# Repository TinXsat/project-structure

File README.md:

# project-structure

This repo is purely for discussing and planning the whole project's structure - what will communicate with what and how, how software will be organised, etc - whole "schema"

### Contributing :pencil:
All discusion and changes will be done through Pull Requests and Issues - commiting directly to master is officially illegal here  :no_entry_sign: :hand: :no_entry:

<sub><sub>[Inserting emojis](https://gist.github.com/rxaviers/7360908) into every single header is also required, and not respecting that will be punished 🔪 </sub></sub>

<!-- START doctoc generated TOC please keep comment here to allow auto update -->
<!-- DON'T EDIT THIS SECTION, INSTEAD RE-RUN doctoc TO UPDATE -->
**Table of Contents**

- [Mission :rainbow:](#mission-rainbow)
  - [Measurements of atmospheric pressure and temperature with subsequent data analysis :thermometer:](#measurements-of-atmospheric-pressure-and-temperature-with-subsequent-data-analysis-thermometer)
    - [Key goals :key:](#key-goals-key)
  - [Demonstration of cansat system for rescue operations during natural disasters :volcano:](#demonstration-of-cansat-system-for-rescue-operations-during-natural-disasters-volcano)
    - [Key goals :key:](#key-goals-key-1)
    - [Optional goals :small_blue_diamond:](#optional-goals-small_blue_diamond)
- [Satellite :satellite:](#satellite-satellite)
  - [Satellite launch :rocket:](#satellite-launch-rocket)
  - [Sensors aboard :thermometer:](#sensors-aboard-thermometer)
  - [Satellite 2 ground communication :phone:](#satellite-2-ground-communication-phone)
- [Ground station :radio:](#ground-station-radio)
- [Ground back-end server :computer:](#ground-back-end-server-computer)
- [Front-end :iphone:](#front-end-iphone)
- [Further data analisys :bar_chart:](#further-data-analisys-bar_chart)
- [Gantt timeline chart :alarm_clock:](#gantt-timeline-chart-alarm_clock)

<!-- END doctoc generated TOC please keep comment here to allow auto update -->

# Mission :rainbow:
## Measurements of atmospheric pressure and temperature with subsequent data analysis :thermometer:

### Key goals :key:

 - Measure of pressure and temperature outside the cansat.
 - Radio transmission of measurements data in minimal rate one packet per second.
 - Calculation of altitude based on atmospheric pressure.

## Demonstration of cansat system for rescue operations during natural disasters :volcano:

### Key goals :key:

 - Design system that meet following requirements:
 - low cost of produce
 - high accuracy
 - Access to information about position(GPS), altitude (barometer), temperature, acceleration
 - Take photos from the thermovision and visible range camera.
 - Mark on photos all obstacles (to protect rescuers) and places where people could possibly be.

### Optional goals :small_blue_diamond:

 - Investigate fire resistant biofiber composite with which body of cansat will be build
 - Pointing geographical coordinates of marked obstacles/humans.

# Satellite :satellite:
How the cansat sattelite will look and work to help us do the mission?

## Satellite launch :rocket:
How we will actually launching the sattelite (that is take it to 1.5km above)?

## Sensors aboard :thermometer:

## Satellite 2 ground communication :phone:
How our satellite will communicate with the ground station?

# Ground station :radio:
What is ground station and how it will work and pass us *the data* :chart_with_upwards_trend:?

# Ground back-end server :computer:
[Back-end server](https://github.com/TinXsat/server) takes care of receiving data from [ground station](#ground-station-radio),
parsing and processing it, and serving it to the [front-end](#front-end-iphone).
It also caches and saves any data that it received, in case satellite would fall apart

It is written in [Python](https://www.python.org/), and uses [Flask](https://flask.palletsprojects.com/) to serve a REST API

# Front-end :iphone:
[Our front-end](https://github.com/TinXsat/frontend) is a dashboard that will show us what is currently happening with the sattelite while it's in the air - for example, a map showing where the sattelite is right now, animation (like at SpaceX) about in what stage of the mission it currently is, etc

It is built in Flutter, and compiled to a web app. It gets data form [the server](#ground-back-end-server-computer) through REST endpoints, probably instantly, through localhost, since they will be hosted on same computer

# Further data analisys :bar_chart:
What we will further do with *the data* beyond the elements above?

# Gantt timeline chart :alarm_clock:

// You can view the code-block it in [gantt-chart.md](gantt-chart.md)

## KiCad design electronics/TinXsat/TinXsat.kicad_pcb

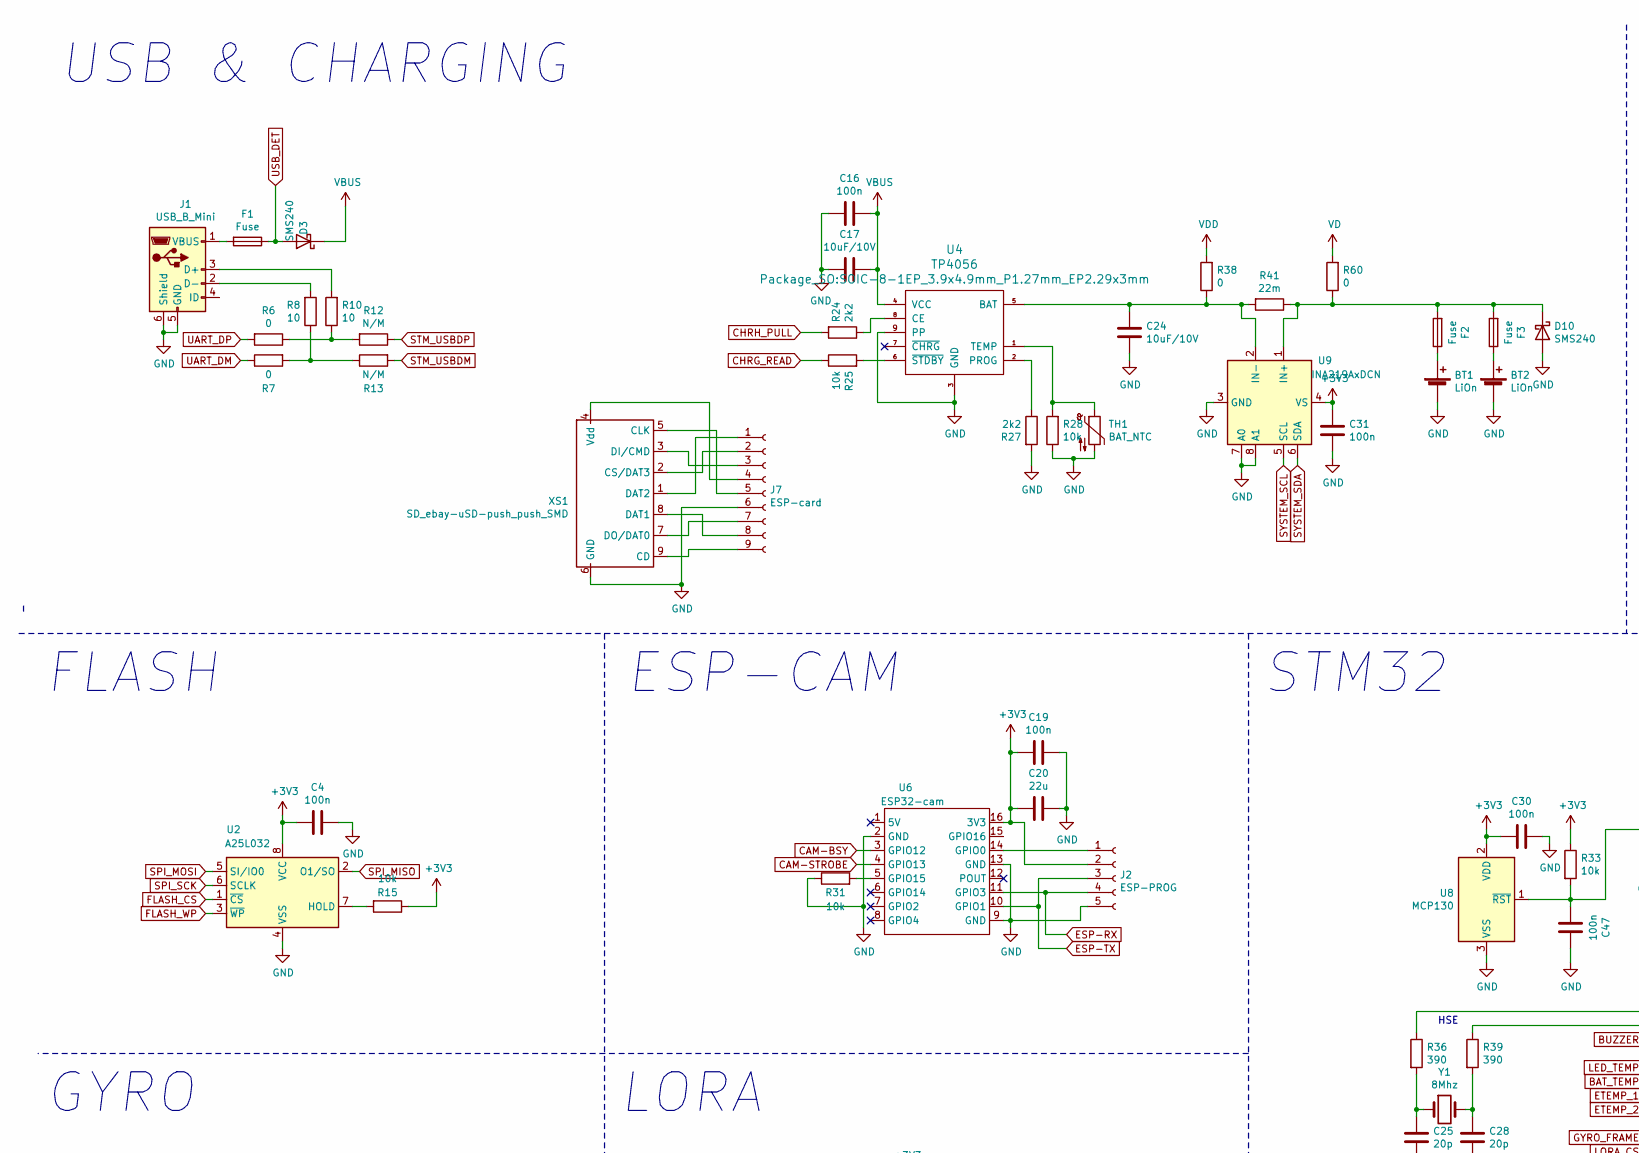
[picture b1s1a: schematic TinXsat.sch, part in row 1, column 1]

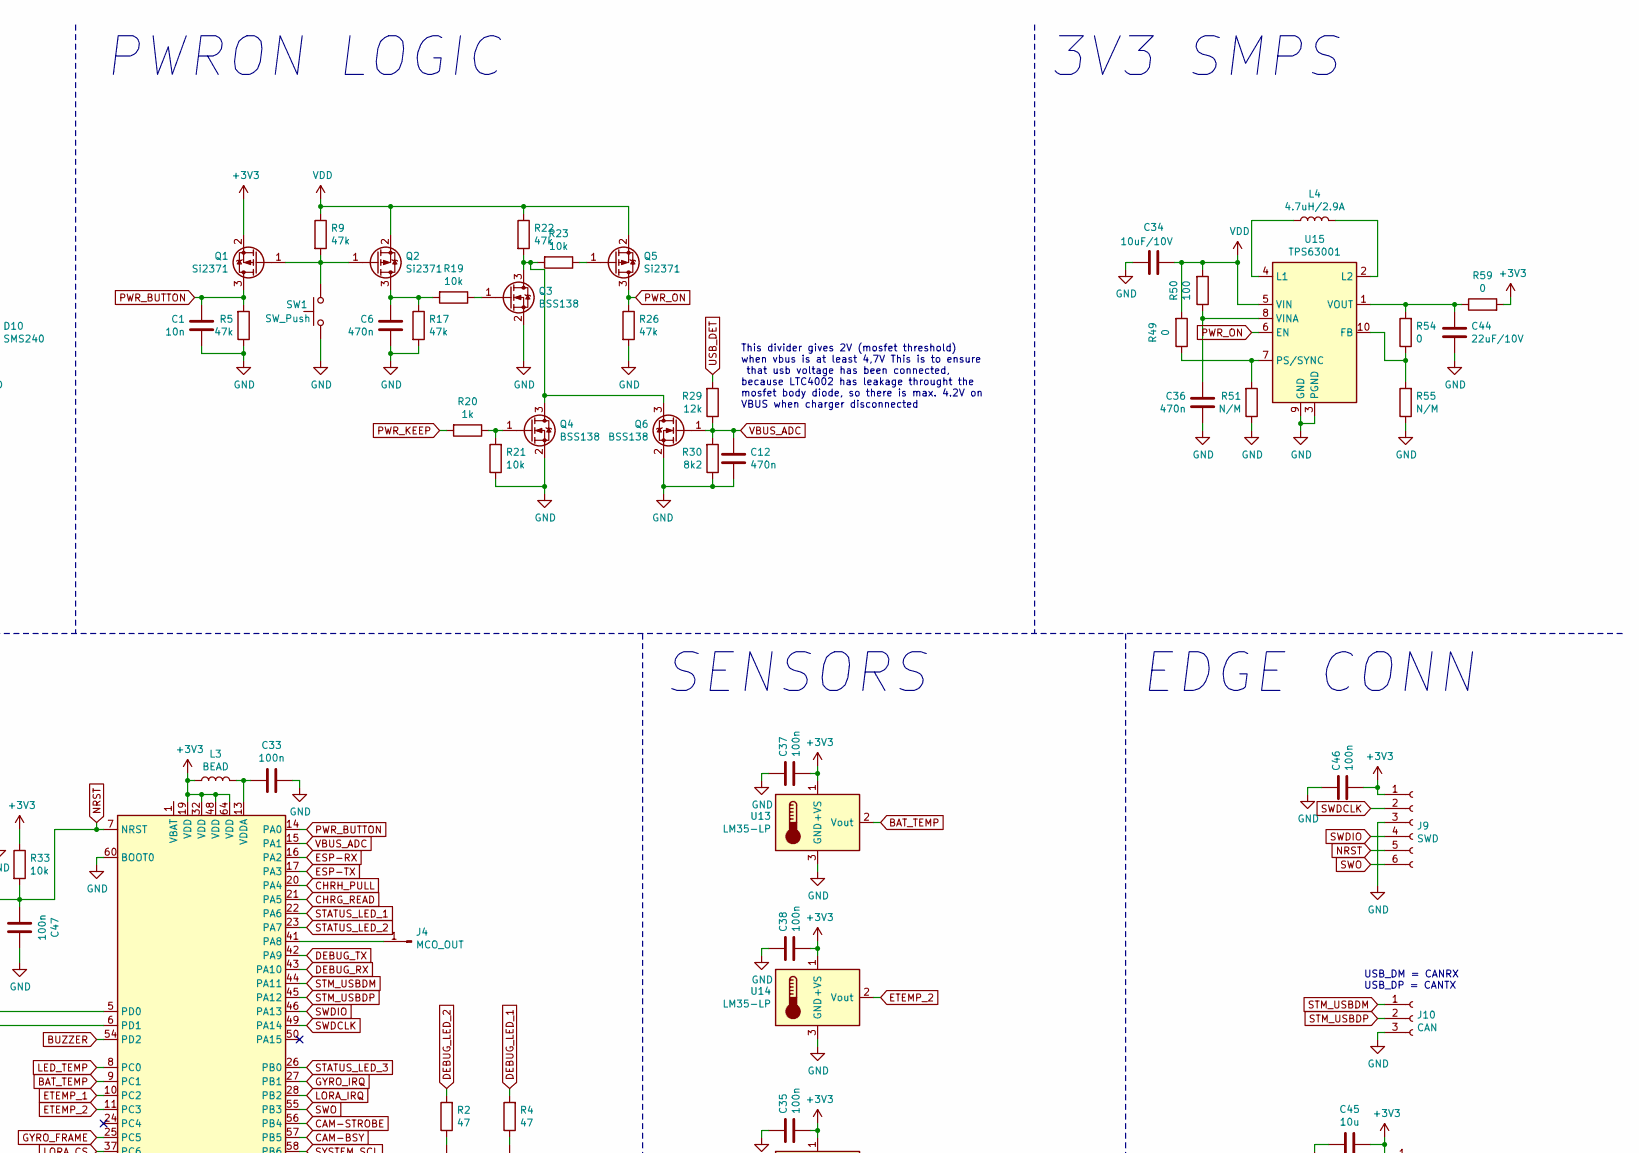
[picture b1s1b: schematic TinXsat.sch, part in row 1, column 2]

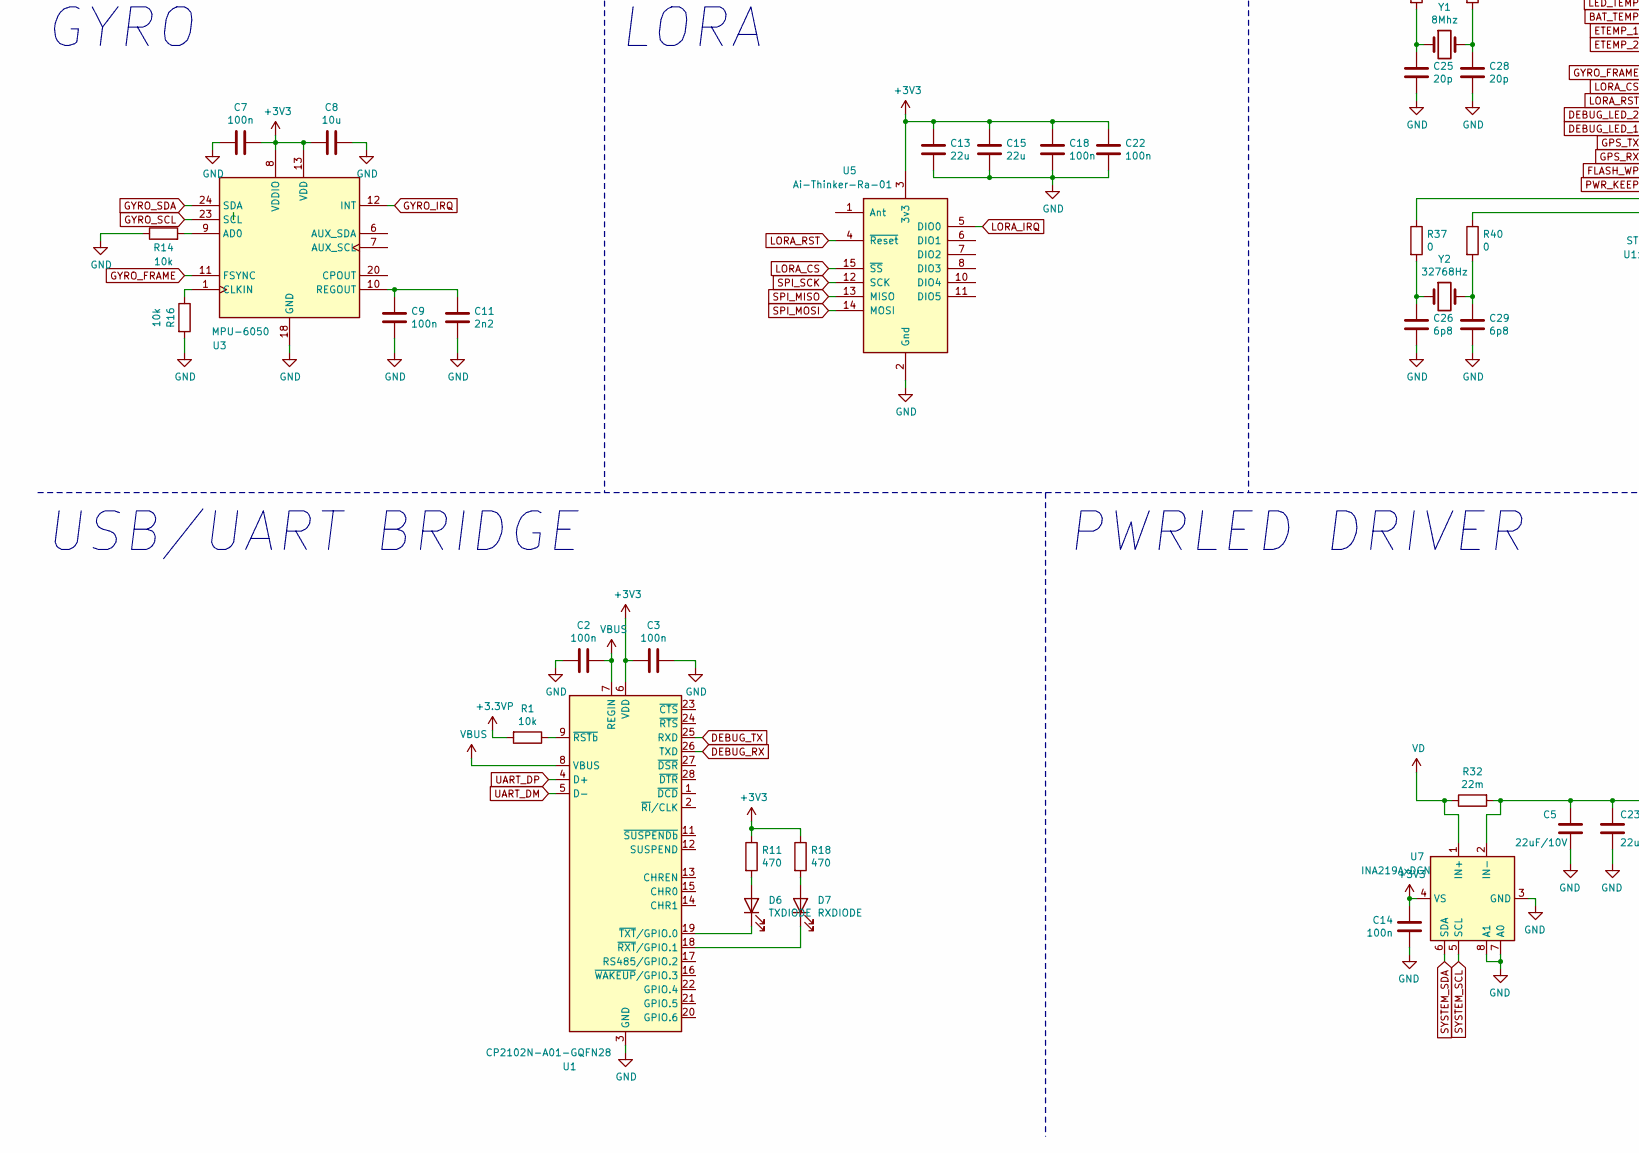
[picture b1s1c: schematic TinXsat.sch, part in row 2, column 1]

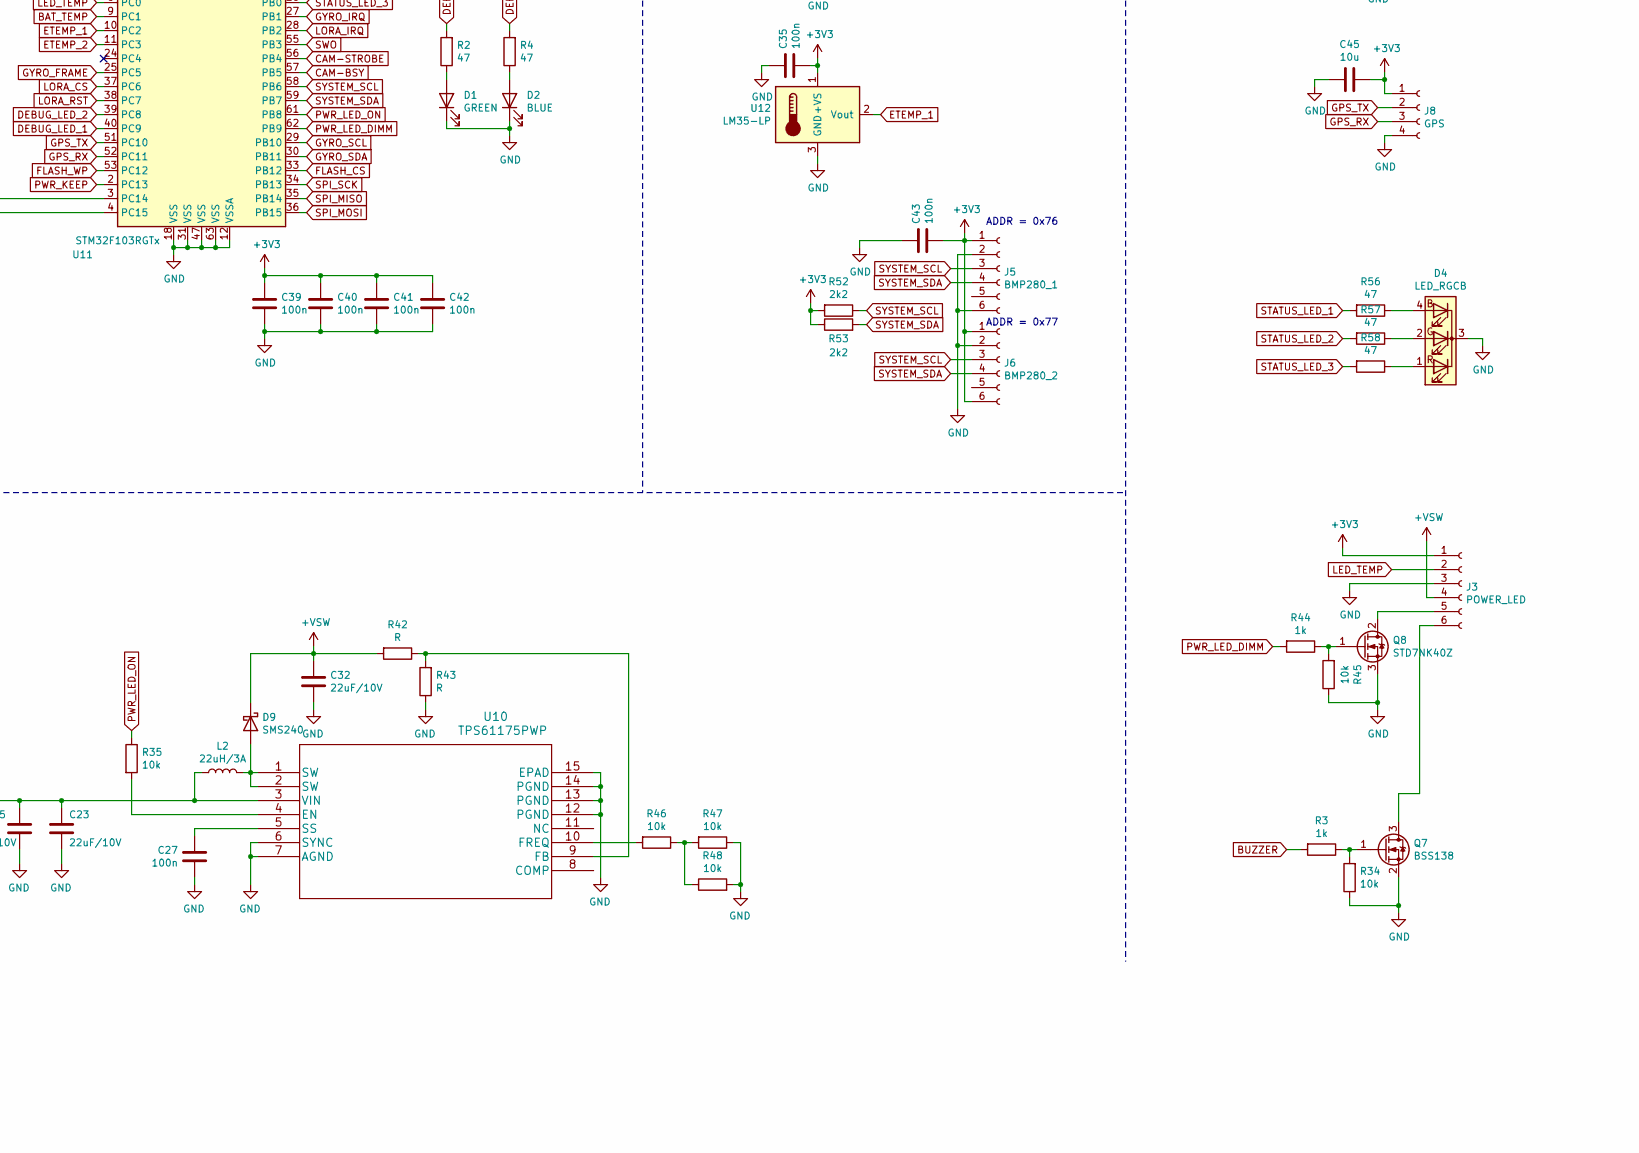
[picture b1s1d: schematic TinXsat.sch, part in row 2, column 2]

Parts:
BT1, BT2: LiOn; BATT
C1: 10n; C_0805_2012Metric_Pad1.18x1.45mm_HandSolder
C2, C3, C4, C7, C9, C14, C16, C18, C19, C22, C27, C30, C31, C33, C35, C37, C38, C39, C40, C41, C42, C43, C46, C47: 100n; C_0805_2012Metric_Pad1.18x1.45mm_HandSolder
C5, C23, C32, C44: 22uF/10V; C_1210_3225Metric_Pad1.33x2.70mm_HandSolder
C6, C12, C36: 470n; C_0805_2012Metric_Pad1.18x1.45mm_HandSolder
C8, C45: 10u; C_1206_3216Metric_Pad1.33x1.80mm_HandSolder
C11: 2n2; C_0805_2012Metric_Pad1.18x1.45mm_HandSolder
C13, C15, C20: 22u; C_1210_3225Metric_Pad1.33x2.70mm_HandSolder
C17, C24, C34: 10uF/10V; C_1206_3216Metric_Pad1.33x1.80mm_HandSolder
C25, C28: 20p; C_0603_1608Metric_Pad1.08x0.95mm_HandSolder
C26, C29: 6p8; C_0603_1608Metric_Pad1.08x0.95mm_HandSolder
D1: GREEN; LED_0805_2012Metric_Pad1.15x1.40mm_HandSolder
D2: BLUE; LED_0805_2012Metric_Pad1.15x1.40mm_HandSolder
D3, D9, D10: SMS240; D_MELF
D4: LED_RGCB; LED_D5.0mm-4_RGB
D6: TXDIODE; LED_0805_2012Metric_Pad1.15x1.40mm_HandSolder
D7: RXDIODE; LED_0805_2012Metric_Pad1.15x1.40mm_HandSolder
F1, F2, F3: Fuse; Fuse_1206_3216Metric_Pad1.42x1.75mm_HandSolder
J1: USB_B_Mini; USB_Mini-B_Lumberg_2486_01_Horizontal
J2: ESP-PROG; PinHeader_1x05_P2mm_SMD
J3: POWER_LED; PinHeader_1x06_P2mm_SMD
J4: MCO_OUT; PinHeader_1x01_P2.54mm_Vertical
J5: BMP280_1; PinHeader_1x06_P2mm_SMD
J6: BMP280_2; PinHeader_1x06_P2mm_SMD
J7: ESP-card; PinHeader_1x08_P2mm_SMD
J8: GPS; PinHeader_1x04_P2mm_SMD
J9: SWD; PinHeader_1x06_P2mm_SMD
J10: CAN; PinHeader_1x03_P2mm_SMD
L2: 22uH/3A; L_7.3x7.3_H3.5
L3: BEAD; L_0805_2012Metric_Pad1.05x1.20mm_HandSolder
L4: 4.7uH/2.9A; L_7.3x7.3_H3.5
Q1, Q2, Q5: Si2371; SOT-23
Q3, Q4, Q6, Q7: BSS138; SOT-23
Q8: STD7NK40Z; TO-252-2
R1, R14, R15, R16, R19, R21, R23, R25, R28, R31, R33, R34, R35, R45, R46, R47, R48: 10k; R_0805_2012Metric_Pad1.20x1.40mm_HandSolder
R2, R4, R56, R57, R58: 47; R_0805_2012Metric_Pad1.20x1.40mm_HandSolder
R3, R20, R44: 1k; R_0805_2012Metric_Pad1.20x1.40mm_HandSolder
R5, R9, R17, R22, R26: 47k; R_0805_2012Metric_Pad1.20x1.40mm_HandSolder
R6, R7, R37, R38, R40, R49, R54, R59, R60: 0; R_0805_2012Metric_Pad1.20x1.40mm_HandSolder
R8, R10: 10; R_0805_2012Metric_Pad1.20x1.40mm_HandSolder
R11, R18: 470; R_0805_2012Metric_Pad1.20x1.40mm_HandSolder
R12, R13, R51, R55: N/M; R_0805_2012Metric_Pad1.20x1.40mm_HandSolder
R24, R27, R52, R53: 2k2; R_0805_2012Metric_Pad1.20x1.40mm_HandSolder
R29: 12k; R_0805_2012Metric_Pad1.20x1.40mm_HandSolder
R30: 8k2; R_0805_2012Metric_Pad1.20x1.40mm_HandSolder
R32, R41: 22m; R_MiniMELF_MMA-0204
R36, R39: 390; R_0805_2012Metric_Pad1.20x1.40mm_HandSolder
R42, R43: R; R_0805_2012Metric_Pad1.20x1.40mm_HandSolder
R50: 100; R_0805_2012Metric_Pad1.20x1.40mm_HandSolder
SW1: SW_Push; SW_Tactile_SKHH_Angled
TH1: BAT_NTC; PinHeader_1x02_P2mm_SMD
U1: CP2102N-A01-GQFN28; QFN-28-1EP_5x5mm_P0.5mm_EP3.35x3.35mm
U2: A25L032; WSON-8-1EP_6x5mm_P1.27mm_EP3.4x4mm
U3: MPU-6050; InvenSense_QFN-24_4x4mm_P0.5mm
U4: TP4056; SOIC-8-1EP_3.9x4.9mm_P1.27mm_EP2.29x3mm
U5: Ai-Thinker-Ra-01; Ai-Thinker-Ra-01-LoRa
U6: ESP32-cam; ESP32-CAM
U7, U9: INA219AxDCN; SOT-23-8
U8: MCP130; SOT-23
U10: TPS61175PWP
U11: STM32F103RGTx; LQFP-64_10x10mm_P0.5mm
U12, U13, U14: LM35-LP; PinHeader_1x03_P2mm_SMD
U15: TPS63001; Texas_DRC0010J_ThermalVias
XS1: SD_ebay-uSD-push_push_SMD; Conn_uSDcard
Y1: 8Mhz; Crystal_SMD_HC49-SD
Y2: 32768Hz; Crystal_DS26_D2.0mm_L6.0mm_Horizontal_1EP_style1

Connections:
+3.3VP: R1.2
+3V3: C3.2, C4.2, C7.1, C8.2, C13.2, C14.2, C15.2, C18.2, C19.1, C20.2, C22.2, C30.1, C31.2, C35.1, C37.1, C38.1, C39.2, C40.2, C41.2, C42.2, C43.1, C45.1, C46.1, J2.2, J3.1, J5.1, J6.1, J6.6, J8.1, J9.1, L3.1, Q1.2 (S), R11.1, R15.1, R18.1, R33.1, R52.2, R53.1, R59.2, U1.6 (VDD), U2.8 (VCC), U3.8 (VDDIO), U3.13 (VDD), U5.3 (3v3), U6.16 (3V3), U7.4 (VS), U8.2 (VDD), U9.4 (VS), U11.19 (VDD), U11.32 (VDD), U11.48 (VDD), U11.64 (VDD), U12.1 (+VS), U13.1 (+VS), U14.1 (+VS)
+VSW: C32.1, D9.1 (K), J3.4, R42.2
BAT_TEMP: U11.9 (PC1), U13.2 (Vout)
BUZZER: R3.2, U11.54 (PD2)
CAM-BSY: U6.3 (GPIO12), U11.57 (PB5)
CAM-STROBE: U6.4 (GPIO13), U11.56 (PB4)
CHRG_READ: R25.1, U11.21 (PA5)
CHRH_PULL: R24.2, U11.20 (PA4)
DEBUG_LED_1: R4.2, U11.40 (PC9)
DEBUG_LED_2: R2.2, U11.39 (PC8)
DEBUG_RX: U1.26 (TXD), U11.43 (PA10)
DEBUG_TX: U1.25 (RXD), U11.42 (PA9)
ESP-RX: J2.4, U6.11 (GPIO3), U11.16 (PA2)
ESP-TX: J2.3, U6.10 (GPIO1), U11.17 (PA3)
ETEMP_1: U11.10 (PC2), U12.2 (Vout)
ETEMP_2: U11.11 (PC3), U14.2 (Vout)
FLASH_CS: U2.1 (~CS), U11.33 (PB12)
FLASH_WP: U2.3 (~WP~), U11.53 (PC12)
GND: BT1.2 (-), BT2.2 (-), C1.1, C2.2, C3.1, C4.1, C5.2, C6.1, C7.2, C8.1, C9.1, C11.1, C12.2, C13.1, C14.1, C15.1, C16.2, C17.1, C18.1, C19.2, C20.1, C22.1, C23.2, C24.2, C25.2, C26.2, C27.1, C28.2, C29.2, C30.2, C31.1, C32.2, C33.2, C34.2, C35.2, C36.1, C37.2, C38.2, C39.1, C40.1, C41.1, C42.1, C43.2, C44.2, C45.2, C46.2, C47.2, D1.1 (K), D2.1 (K), D4.3 (K), D10.2 (A), J1.5 (GND), J1.6 (Shield), J2.5, J3.3, J5.2, J5.6, J6.2, J7.6, J8.4, J9.3, J10.3, Q3.2 (S), Q4.2 (S), Q6.2 (S), Q7.2 (S), Q8.3 (S), R5.1, R14.1, R16.2, R17.2, R21.1, R26.2, R27.2, R28.1, R30.1, R31.1, R34.1, R43.1, R45.1, R47.1, R48.2, R51.1, R55.1, SW1.2, TH1.2, U1.3 (GND), U1.29 (GND), U2.4 (VSS), U3.18 (GND), U4.3 (GND), U4.9 (PP), U5.2 (Gnd), U5.9 (Gnd), U5.16 (Gnd), U6.2 (GND), U6.9 (GND), U6.13 (GND), U7.3 (GND), U7.7 (A0), U7.8 (A1), U8.3 (VSS), U9.3 (GND), U9.7 (A0), U9.8 (A1), U10.6 (SYNC), U10.7 (AGND), U10.12 (PGND), U10.13 (PGND), U10.14 (PGND), U10.15 (EPAD), U11.12 (VSSA), U11.18 (VSS), U11.31 (VSS), U11.47 (VSS), U11.60 (BOOT0), U11.63 (VSS), U12.3 (GND), U13.3 (GND), U14.3 (GND), U15.3 (PGND), U15.9 (GND), U15.11 (PGND), XS1.6 (GND)
GPS_RX: J8.3, U11.52 (PC11)
GPS_TX: J8.2, U11.51 (PC10)
GYRO_FRAME: U3.11 (FSYNC), U11.25 (PC5)
GYRO_IRQ: U3.12 (INT), U11.27 (PB1)
GYRO_SCL: U3.23 (SCL), U11.29 (PB10)
GYRO_SDA: U3.24 (SDA), U11.30 (PB11)
LED_TEMP: J3.2, U11.8 (PC0)
LORA_CS: U5.15 (~SS), U11.37 (PC6)
LORA_IRQ: U5.5 (DIO0), U11.28 (PB2)
LORA_RST: U5.4 (~Reset), U11.38 (PC7)
NRST: C47.1, J9.5, R33.2, U8.1 (~RST), U11.7 (NRST)
unnamed: BT1.1 (+), F2.1
unnamed: BT2.1 (+), F3.1
unnamed: C6.2, Q2.3 (D), R17.1, R19.2
unnamed: C9.2, C11.2, U3.10 (REGOUT)
unnamed: C5.1, C23.1, L2.1, R32.2, U7.2 (IN-), U10.3 (VIN)
unnamed: C24.1, R38.1, R41.2, U4.5 (BAT), U9.2 (IN-)
unnamed: C25.1, R36.2, Y1.1
unnamed: C26.1, R37.2, Y2.1
unnamed: C27.2, U10.5 (SS)
unnamed: C28.1, R39.2, Y1.2
unnamed: C29.1, R40.2, Y2.2
unnamed: C33.1, L3.2, U11.13 (VDDA)
unnamed: C36.2, R50.1, U15.8 (VINA)
unnamed: C44.1, R54.2, R59.1, U15.1 (VOUT)
unnamed: D1.2 (A), R2.1
unnamed: D2.2 (A), R4.1
unnamed: D4.1 (RA), R58.1
unnamed: D4.2 (GA), R57.1
unnamed: D4.4 (BA), R56.1
unnamed: D6.1 (K), U1.19 (~TXT~/GPIO.0)
unnamed: D6.2 (A), R11.2
unnamed: D7.1 (K), U1.18 (~RXT~/GPIO.1)
unnamed: D7.2 (A), R18.2
unnamed: D9.2 (A), L2.2, U10.1 (SW), U10.2 (SW)
unnamed: D10.1 (K), F2.2, F3.2, R41.1, R60.1, U9.1 (IN+)
unnamed: F1.2, J1.1 (VBUS)
unnamed: J1.2 (D-), R8.2
unnamed: J1.3 (D+), R10.2
unnamed: J2.1, U6.14 (GPIO0)
unnamed: J3.5, Q8.2 (D)
unnamed: J3.6, Q7.3 (D)
unnamed: J4.1, U11.41 (PA8)
unnamed: J7.1, XS1.1 (DAT2)
unnamed: J7.2, XS1.2 (CS/DAT3)
unnamed: J7.3, XS1.3 (DI/CMD)
unnamed: J7.4, XS1.4 (Vdd)
unnamed: J7.5, XS1.5 (CLK)
unnamed: J7.7, XS1.7 (DO/DAT0)
unnamed: J7.8, XS1.8 (DAT1)
unnamed: J7.9, XS1.9 (CD)
unnamed: L4.1, U15.4 (L1)
unnamed: L4.2, U15.2 (L2)
unnamed: Q1.1 (G), Q2.1 (G), R9.2, SW1.1
unnamed: Q3.1 (G), R19.1
unnamed: Q3.3 (D), Q4.3 (D), Q6.3 (D), R22.2, R23.2
unnamed: Q4.1 (G), R20.1, R21.2
unnamed: Q5.1 (G), R23.1
unnamed: Q7.1 (G), R3.1, R34.2
unnamed: Q8.1 (G), R44.1, R45.2
unnamed: R1.1, U1.9 (~RSTb)
unnamed: R6.1, R10.1, R12.2
unnamed: R7.2, R8.1, R13.1
unnamed: R14.2, U3.9 (AD0)
unnamed: R15.2, U2.7 (HOLD)
unnamed: R16.1, U3.1 (CLKIN)
unnamed: R24.1, U4.8 (CE)
unnamed: R25.2, U4.6 (~STDBY)
unnamed: R27.1, U4.2 (PROG)
unnamed: R28.2, TH1.1, U4.1 (TEMP)
unnamed: R31.2, U6.5 (GPIO15)
unnamed: R35.2, U10.4 (EN)
unnamed: R36.1, U11.5 (PD0)
unnamed: R37.1, U11.3 (PC14)
unnamed: R39.1, U11.6 (PD1)
unnamed: R40.1, U11.4 (PC15)
unnamed: R42.1, R43.2, U10.9 (FB)
unnamed: R46.1, R47.2, R48.1
unnamed: R46.2, U10.10 (FREQ)
unnamed: R49.1, R51.2, U15.7 (PS/SYNC)
unnamed: R54.1, R55.2, U15.10 (FB)
PWR_BUTTON: C1.2, Q1.3 (D), R5.2, U11.14 (PA0)
PWR_KEEP: R20.2, U11.2 (PC13)
PWR_LED_DIMM: R44.2, U11.62 (PB9)
PWR_LED_ON: R35.1, U11.61 (PB8)
PWR_ON: Q5.3 (D), R26.1, U15.6 (EN)
SPI_MISO: U2.2 (O1/SO), U5.13 (MISO), U11.35 (PB14)
SPI_MOSI: U2.5 (SI/IO0), U5.14 (MOSI), U11.36 (PB15)
SPI_SCK: U2.6 (SCLK), U5.12 (SCK), U11.34 (PB13)
STATUS_LED_1: R56.2, U11.22 (PA6)
STATUS_LED_2: R57.2, U11.23 (PA7)
STATUS_LED_3: R58.2, U11.26 (PB0)
STM_USBDM: J10.1, R13.2, U11.44 (PA11)
STM_USBDP: J10.2, R12.1, U11.45 (PA12)
SWDCLK: J9.2, U11.49 (PA14)
SWDIO: J9.4, U11.46 (PA13)
SWO: J9.6, U11.55 (PB3)
SYSTEM_SCL: J5.3, J6.3, R52.1, U7.5 (SCL), U9.5 (SCL), U11.58 (PB6)
SYSTEM_SDA: J5.4, J6.4, R53.2, U7.6 (SDA), U9.6 (SDA), U11.59 (PB7)
UART_DM: R7.1, U1.5 (D-)
UART_DP: R6.2, U1.4 (D+)
USB_DET: D3.2 (A), F1.1, R29.2
VBUS: C2.1, C16.1, C17.2, D3.1 (K), U1.7 (REGIN), U1.8 (VBUS), U4.4 (VCC)
VBUS_ADC: C12.1, Q6.1 (G), R29.1, R30.2, U11.15 (PA1)
VD: R32.1, R60.2, U7.1 (IN+)
VDD: C34.1, Q2.2 (S), Q5.2 (S), R9.1, R22.1, R38.2, R49.2, R50.2, U15.5 (VIN)

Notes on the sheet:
This divider gives 2V (mosfet threshold) when vbus is at least 4,7V This is to ensure that usb voltage has been connected, because LTC4002 has leakage throught the mosfet body diode, so there is max. 4.2V on VBUS when charger disconnected
USB_DM = CANRX USB_DP = CANTX
HSE
ADDR = 0x76
ADDR = 0x77
STM32
ESP-CAM
FLASH
GYRO
LORA
SENSORS
EDGE CONN
3V3 SMPS
PWRON LOGIC
USB & CHARGING
USB/UART BRIDGE
PWRLED DRIVER

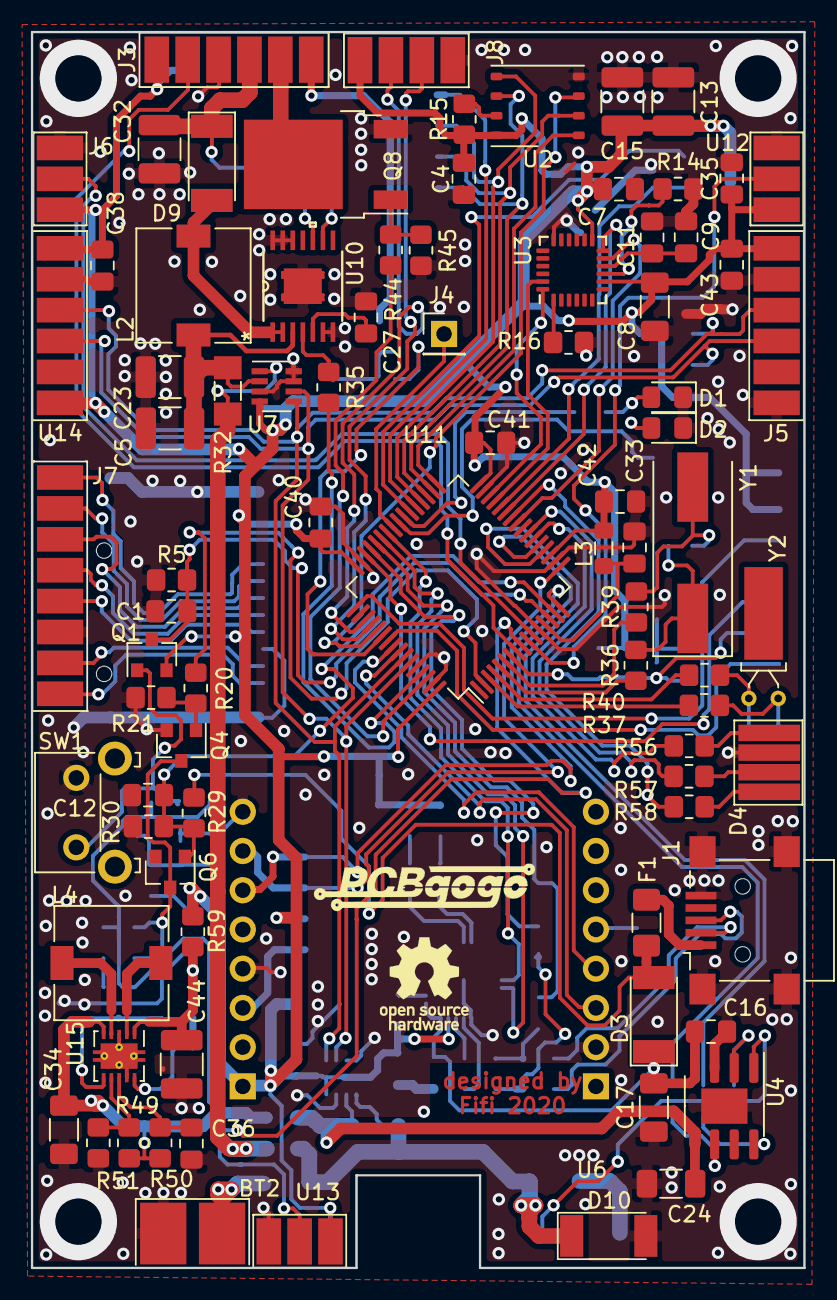
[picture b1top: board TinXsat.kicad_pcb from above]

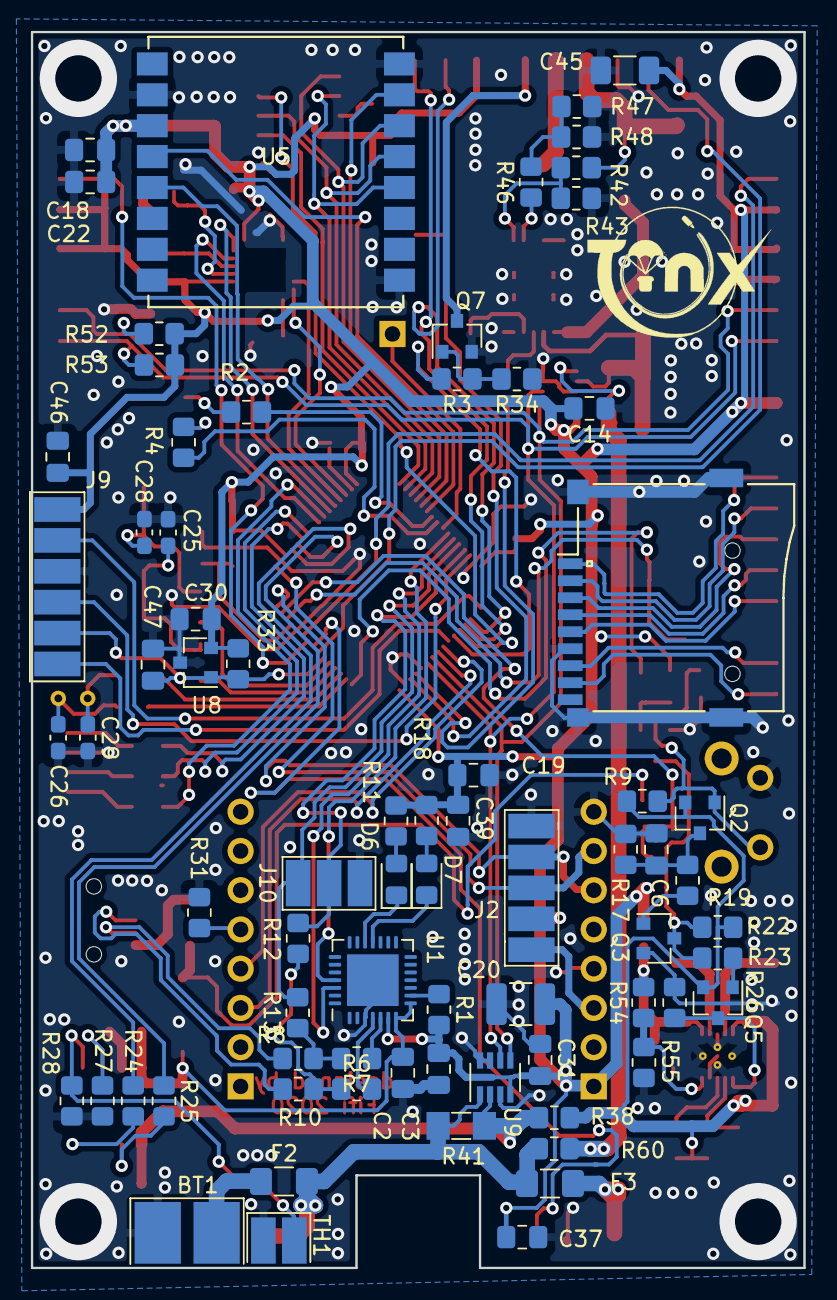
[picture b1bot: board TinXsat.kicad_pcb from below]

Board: 2 copper layers, 50.0 x 80.0 mm, 159 parts (74 on the bottom side), 124 nets.

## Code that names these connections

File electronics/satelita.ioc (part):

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Mcu.Name=STM32F103R(F-G)Tx
Mcu.Package=LQFP64
Mcu.UserName=STM32F103RGTx
PA0-WKUP.GPIOParameters=GPIO_Label
PA0-WKUP.GPIO_Label=PWR_WKUP
PA0-WKUP.Mode=SYS_WakeUp0
PA0-WKUP.Signal=SYS_WKUP
PA1.GPIOParameters=GPIO_Label
PA1.GPIO_Label=USB_DETECT
PA1.Signal=ADCx_IN1
PA10.GPIOParameters=GPIO_Label
PA10.GPIO_Label=DEBUG_RX
PA10.Signal=USART1_RX
PA11.GPIOParameters=GPIO_Label
PA11.GPIO_Label=USB_DM - CAN_RX
PA11.Mode=Device
PA11.Signal=USB_DM
PA12.GPIOParameters=GPIO_Label
PA12.GPIO_Label=USB_DP - CAN TX
PA12.Mode=Device
PA12.Signal=USB_DP
PA13.Signal=SYS_JTMS-SWDIO
PA14.Signal=SYS_JTCK-SWCLK
PA2.GPIOParameters=GPIO_Label
PA2.GPIO_Label=ESP_TX
PA2.Signal=USART2_TX
PA3.GPIOParameters=GPIO_Label
PA3.GPIO_Label=ESP_RX
PA3.Signal=USART2_RX
PA4.GPIOParameters=GPIO_Label
PA4.GPIO_Label=CHARGE_0
PA4.Signal=GPIO_Output
PA5.GPIOParameters=GPIO_Label
PA5.GPIO_Label=CHARGE_1
PA5.Signal=GPIO_Input
PA6.GPIOParameters=GPIO_Label
PA6.GPIO_Label=STATUS_LED_CH0
PA6.Signal=S_TIM3_CH1
PA7.GPIOParameters=GPIO_Label
PA7.GPIO_Label=STATUS_LED_CH2
PA7.Signal=S_TIM3_CH2
PA8.GPIOParameters=GPIO_Label
PA8.GPIO_Label=MCO_SYSCLK
PA8.Mode=Clock-out
PA8.Signal=RCC_MCO
PA9.GPIOParameters=GPIO_Label
PA9.GPIO_Label=DEBUG_TX
PA9.Signal=USART1_TX
PB0.GPIOParameters=GPIO_Label
PB0.GPIO_Label=STATUS_LED_CH3
PB0.Signal=S_TIM3_CH3
PB1.GPIOParameters=GPIO_Label
PB1.GPIO_Label=GYRO_IRQ
PB1.Signal=GPIO_Input
PB10.GPIOParameters=GPIO_Label
PB10.GPIO_Label=CAMERA_TX
PB10.Signal=USART3_TX
PB11.GPIOParameters=GPIO_Label
PB11.GPIO_Label=CAMERA_RX
PB11.Signal=USART3_RX
PB12.GPIOParameters=GPIO_Label
PB12.GPIO_Label=FLASH_CS
PB12.Signal=GPIO_Output
PB13.GPIOParameters=GPIO_Label
PB13.GPIO_Label=FLASH_LORA_GYRO_SCK
PB13.Signal=SPI2_SCK
PB14.GPIOParameters=GPIO_Label
PB14.GPIO_Label=FLASH_LORA_GYRO_MISO
PB14.Signal=SPI2_MISO
PB15.GPIOParameters=GPIO_Label
PB15.GPIO_Label=FLASH_LORA_GYRO_MOSI
PB15.Signal=SPI2_MOSI
PB2.GPIOParameters=GPIO_Label
PB2.GPIO_Label=LORA_IRQ
PB2.Signal=GPIO_Input
PB3.Signal=SYS_JTDO-TRACESWO
PB4.GPIOParameters=GPIO_Label
PB4.GPIO_Label=CAMERA_STROBE
PB4.Signal=GPIO_Output
PB5.GPIOParameters=GPIO_Label
PB5.GPIO_Label=CAMERA_BUSY
PB5.Signal=GPIO_Input
PB6.GPIOParameters=GPIO_Label
PB6.GPIO_Label=SYSTEM_I2C_SCL
PB6.Signal=I2C1_SCL
PB7.GPIOParameters=GPIO_Label
PB7.GPIO_Label=SYSTEM_I2C_SDA
PB7.Signal=I2C1_SDA
PB8.GPIOParameters=GPIO_Label
PB8.GPIO_Label=PWRLED_ON
PB8.Signal=GPIO_Output
PB9.GPIOParameters=GPIO_Label
PB9.GPIO_Label=PWRLED_DIMM
PB9.Signal=S_TIM4_CH4
PC0.GPIOParameters=GPIO_Label
PC0.GPIO_Label=ATEMP_0
PC0.Signal=ADCx_IN10
PC1.GPIOParameters=GPIO_Label
PC1.GPIO_Label=ATEMP_1
PC1.Signal=ADCx_IN11
PC10.GPIOParameters=GPIO_Label
PC10.GPIO_Label=GPS_TX
PC10.Signal=UART4_TX
PC11.GPIOParameters=GPIO_Label
PC11.GPIO_Label=GPS_RX
PC11.Signal=UART4_RX
PC13-TAMPER-RTC.GPIOParameters=GPIO_Label
PC13-TAMPER-RTC.GPIO_Label=PWR_KEEP
PC13-TAMPER-RTC.Signal=GPIO_Output
PC14-OSC32_IN.Signal=RCC_OSC32_IN
PC15-OSC32_OUT.Signal=RCC_OSC32_OUT
PC2.GPIOParameters=GPIO_Label
PC2.GPIO_Label=ATEMP_2
PC2.Signal=ADCx_IN12
PC3.GPIOParameters=GPIO_Label
PC3.GPIO_Label=ATEMP_3
PC3.Signal=ADCx_IN13
PC4.GPIOParameters=GPIO_Label
PC4.GPIO_Label=GYRO_CS
PC4.Signal=GPIO_Output
PC5.GPIOParameters=GPIO_Label
PC5.GPIO_Label=GYRO_FRAME
PC5.Signal=GPIO_Output
PC6.GPIOParameters=GPIO_Label
PC6.GPIO_Label=LORA_CS
PC6.Signal=GPIO_Output
PC7.GPIOParameters=GPIO_Label
PC7.GPIO_Label=LORA_RST
PC7.Signal=GPIO_Output
PC8.GPIOParameters=GPIO_Label
PC8.GPIO_Label=LED_DEBUG2
PC8.Signal=GPIO_Output
PC9.GPIOParameters=GPIO_Label
PC9.GPIO_Label=LED_DEBUG1
PC9.Signal=GPIO_Output
PD0-OSC_IN.Signal=RCC_OSC_IN
PD1-OSC_OUT.Signal=RCC_OSC_OUT
board=custom

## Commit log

2020-10-11 Create inital readme structure
2020-10-11 Fix table of contents
2020-10-11 Create greetings action
    This will greet and introduce new contributors when they make an issue or pull request
2020-10-11 Add more info about making PRs
2020-10-11 Change greeting messages
2020-10-11 Create action that will generate TOC
2020-10-11 Update readme to include comments for doctoc
2020-10-11 Let's try without token
2020-10-11 docs: update TOC
2020-10-11 Change commit message in TOC
2020-10-11 Remove my manually typed TOC header
    since doctoc will generate it from now
2020-10-11 Add note about toc not working
    Emojis need to stay, no other option. I will make an issue on action
2020-10-11 Change emojis to github-markdown-ish ones
2020-10-11 TOC Bot: Update TOC
2020-10-11 Change emojis to github-markdown-ish
2020-10-11 I'm above the law :sunglasses:
    Remove this line, because it does work :tada:!
2020-10-13 Describe our missions
    resolves #6
2020-10-13 Set proper headers
2020-10-13 Add e m o j i s
2020-10-13 Update greetings.yml
    I'm above the law again :sunglasses:
2020-10-18 Example gantt chart in mermaid
2020-10-18 Create compile-mermaid.yml
    Uses compile-meramid action that... I don't know what will do yet
2020-10-18 Try to change this to see what happens
2020-10-18 Change this to inline?
2020-10-18 Change to what they have in example repo
2020-10-18 Trigger action
2020-10-18 Add compiled mermaid
2020-10-18 Change action to make direct commits
    instead of PRs
2020-10-18 Change branch
2020-10-18 Add comments for any future maintainers
2020-10-18 Action: compile-mermaid
2020-10-18 I'm a dummy
    mermaid compiler didn't distinct between mermaid block in comment vs where it should be, and created... something weird
2020-10-18 Update readme to include gantt-chart.md reference
2020-10-19 Add cron schedule
2020-10-19 Add option to manually trigger this action
2020-10-19 Update gantt-chart.md
    Make plan of gant chart
2020-10-19 Update gantt-chart.md
    Try to repair syntax errors
2020-10-19 Update gantt-chart.md
    Create a design and social works section
2020-10-19 Update gantt-chart.md
    Add Constructing and Testing
2020-10-19 Update gantt-chart.md
    Ready I think
2020-10-26 Add our PDR report
2020-11-17 Add images folder and electronics-description.md
2020-11-17 Add images folder
2020-11-29 added schematic files
2020-12-06 update of pin assigments
2020-12-06 update pin assigments
2020-12-13 pcb initial commit
2020-12-20 pcb update (not finished yet)
2020-12-24 pcb final commit
2020-12-25 pcb gerber commit
2020-12-30 pcb final commit after chinese changes
2021-01-12 Add screenshot
2021-01-12 Add meme
2021-01-12 Add link to server
2021-01-14 Add link to front-end
2021-01-14 Add gantt to readme
2021-01-14 Stop mermaid from flooding me with errors
2021-01-14 Test if mermaid succedes now
2021-01-14 Disable cron and maunal for now, since it's useless :/
2021-01-14 Trigger toc only on markdown change
2021-01-15 Add CDR
    Yay we've ended work!
2021-03-01 Add FDR raport

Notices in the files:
parts and their libraries:
Copyright 2016 Accelerated Designs. All rights reserved.
